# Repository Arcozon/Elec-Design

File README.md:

# Bill of Materials
| Item # | Quantity | Ref | Manufacturer | Manufacturer Part Number |Description | Type
| --: | :--: | :----: | :-----: | :-----: | :-----: | :---: |
| 1 | 1 | R1 | YAGEO | RC0603JR-07330RL | 330 Ω | SMT
| 2 | 2 | R2, R3 | YAGEO | RC0603JR-0710KL | 10 kΩ | SMT
| 3 | 2 | C1, C2 | YAGEO | CC0603JRNPO9BN100 | 10 pF | SMT
| 4 | 3 | C3, C4, C7 | YAGEO | CC0603KRX7R9BB104 | 100 nF | SMT
| 5 | 1 | C6 | YAGEO | CC0603KRX7R9BB104 | 1 uF | SMT
| 6 | 1 | D1 | Hubei KENTO Elec | KT-0603G | Green LED | SMT
| 7 | 1 | D2 | Hubei KENTO Elec | KT-0603R | Red LED | SMT
| 8 | 1 | SW1 | Omron Electronics | B3U-1000P | Push Switch | SMT
| 9 | 1 | Y1 | YXC Crystal Oscillators | X322516MOB4SI | 16 MHz Crystal | SMT
| 10 | 1 | U1 | Microchip Technology | ATmega328P-AN | 32 pin, TQFP Microcontroller  | SMT
| 11 | 2 | J1, J2 | hanxia | HX PH254-01-04-Z-L11.5 straight pin header | 12 pin header, = 2.54mm | THT
| 12 | 1 | J3 | hanxia | HX PH254-01-04-Z-L11.5 straight pin header | 6 pin header, P = 2.54mm | THT

# Pinout
Pins are used and connected, unless specified otherwise
###  U1
| Pin # | Name | Description / Connected to
| --: | :--: | :----: |
| 1 | PD3 | J1-Pin7
| 2 | PD4 | J1-Pin6
| 3 | GND | Ground
| 4 | VCC | Supply voltage
| 5 | GND | Ground, Unused
| 6 | VCC | Supply voltage, Unused
| 7 | XTAL1/PB6 | Oscilation input, Y1-Pin1
| 8 | XTAL2/PB7 | Oscilation input, Y1-Pin3
| 9 | PD5 | J1-Pin5
| 10 | PD6 | J1-Pin4
| 11 | PD7 | J1-Pin3
| 12 | PB0 | J1-Pin2
| 13 | PB1 | J1-Pin1
| 14 | PB2 | Unconnected
| 15 | PB3 | MOSI, J2-Pin11
| 16 | PB4 | MISO, J2-Pin10
| 17 | PB5 | SCK, J2-Pin9
| 18 | AVCC | Supply voltage for ADC
| 19 | ADC6 | Analog input 6, Unconnected
| 20 | AREF | Analog reference
| 21 | GND | Ground, Unused
| 22 | ADC7 | Analog input 7, Unconnected
| 23 | PC0 | Analog input 0, J2-Pin8
| 24 | PC1 | Analog input 1, J2-Pin7
| 25 | PC2 | Analog input 2, J2-Pin6
| 26 | PC3 | Analog input 3, J2-Pin5
| 27 | PC4 | Analog input 4, Unconnected
| 28 | PC5 | Analog input 5, Unconnected
| 29 | RESET/PC6 | Reset signal, J1-Pin10, J2-Pin3, J3-Pin1
| 30 | PD0 | RXI, J1-Pin11, J3-Pin3
| 31 | PD1 | TXO, J1-Pin12, J3-Pin2
| 32 | PD2 | J1-Pin8

###  Y1
| Pin # | Description / Connected to
| --: | :----: |
| 1 | Oscilation output, U1-XTAL1
| 2 | Ground
| 3 | Oscilation output, U1-XTAL2
| 4 | Ground

### J1
| Pin # | Connected to
| --: | :----: |
| 1 | Digital input 9, U1-PB0
| 2 | Digital input 8, U1-PB1
| 3 | Digital input 7, U1-PD7
| 4 | Digital input 6, U1-PD6
| 5 | Digital input 5, U1-PD5
| 6 | Digital input 4, U1-PD4
| 7 | Digital input 3, U1-PD3
| 8 | Digital input 2, U1-PD2
| 9 | Ground
| 10 | U1-Reset, J2-Pin3, J3-Pin1
| 11 | U1-RXI, J3-Pin3
| 12 | U1-TXO, J3-Pin2

### J2
| Pin # | Connected to
| --: | :----: |
| 1 | Power Supply
| 2 | Ground
| 3 | U1-Reset, J1-Pin10, J3-Pin1
| 4 | Supply voltage
| 5 | Analog input 0, U1-PC0
| 6 | Analog input 1, U1-PC1
| 7 | Analog input 2, U1-PC2
| 8 | Analog input 3, U1-PC3
| 9 | U1-PB5, R1
| 10 | MISO, U1-MISO
| 11 | MOSI, U1-MOSI
| 12 | AU1-PB2

### J3
| Pin # | Connected to
| --: | :----: |
| 1 | U1-Reset, J1-Pin10, J2-Pin3
| 2 | U1-TXO, J1-Pin12
| 3 | U1-RXI, J1-Pin11
| 4 | Supply voltage
| 5 | Ground
| 6 | Ground

###  D1, D2
The leds are polarized, the pin order maters
| Pin # | Description
| --: | :----: |
| 1 | Power output
| 2 | Power input
- D1 is connected to Ground (1) and Supply volatage (2)
- D2 is connected to Ground (1) and R1 (2)

### R1, R2, R3
The resistors are not polarized, the pin order does not mater
- R1 is connected to (U1-PB5, J2-Pin9) and D1-P2
- R2 is connected to Ground and D2-P1
- R3 is connected to Supply voltage and (SW1, U1-Reset, J1-Pin10, J2-Pin3)

### C1, C2, C3, C4, C6, C7
The capacitors are not polarized, the pin order does not mater
- C1 is connected to (U1-XTAL1,Y1-Pin1) and Ground
- C2 is connected to (U1-XTAL2,Y1-Pin3) and Ground
- C3 is connected to Supply voltage and U1-AREF
- C4 is connected to SW1 and Ground
- C6 is connected to Supply voltage and Ground
- C7 is connected to Supply voltage and Ground

### SW1
The switch is not polarized, the pin order does not mater
Connected to C4 and (R3, U1-Reset, J1-Pin10, J2-Pin3)

# Notes
- My drawing is a footprint in my lib because i didnt known how to do it otherwise, it also has an error because it has no courtyard
- C5 is missing from provided shematic

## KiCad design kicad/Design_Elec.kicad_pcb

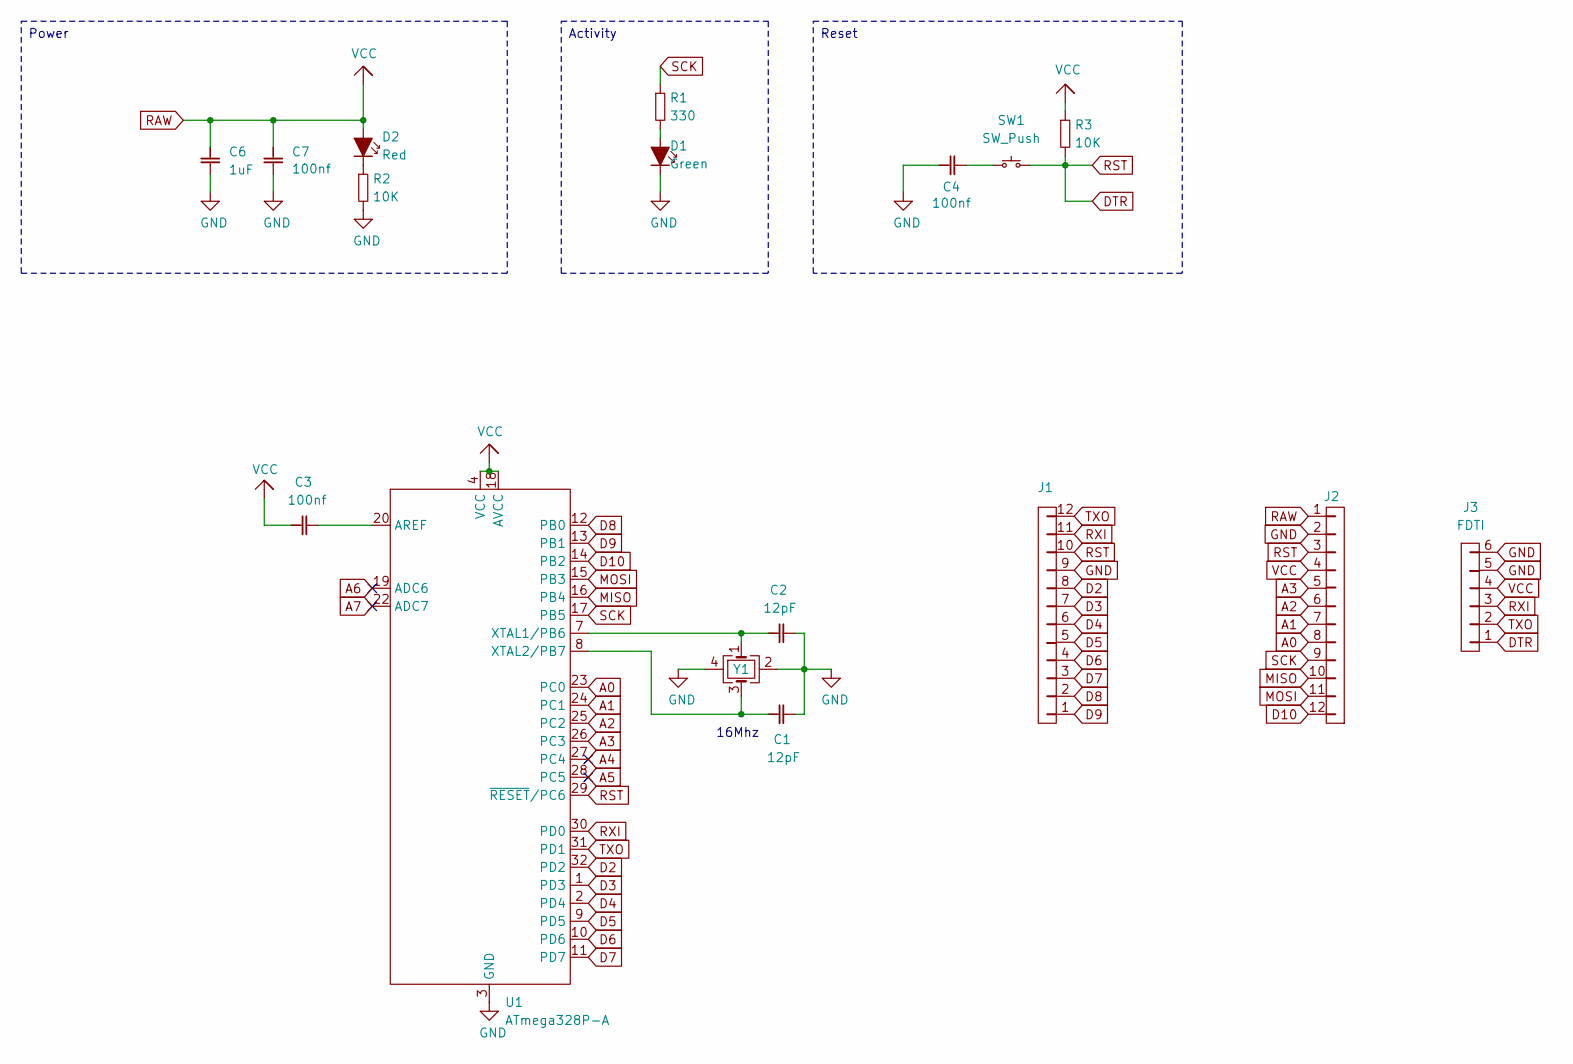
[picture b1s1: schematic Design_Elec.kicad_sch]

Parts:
C1, C2: 12pF; C0603-DA-DimCode_1.7x0.9x0.9mm_P0.4mm
C3, C4, C7: 100nf; C0603-DA-DimCode_1.7x0.9x0.9mm_P0.4mm
C6: 1uF; C0603-DA-DimCode_1.7x0.9x0.9mm_P0.4mm
D1: Green; LED-0603_1.6x0.8x0.6mm_P1.2mm
D2: Red; LED-0603_1.6x0.8x0.6mm_P1.2mm
J1, J2: PinHeader-1x12_30.3x2.5x8.5mm_T3mm_P2.54mm
J3: FDTI; PinHeader-1x06_15.05x2.5x8.5mm_T3mm_P2.54mm
R1: 330; R0603_1.75x0.95x0.55mm_P1.3mm
R2, R3: 10K; R0603_1.75x0.95x0.55mm_P1.3mm
SW1: SW_Push; SW-B3U-1000P_4x2.5x1.7mm_P2.65mm
U1: ATmega328P-A; ATmega328P-AB-TQFP-32_7x7x1.2mm_P0.8mm
Y1: Crystal-YSX321SL_3.2x2.5x0.7mm

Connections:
A0: J2.8, U1.23 (PC0)
A1: J2.7, U1.24 (PC1)
A2: J2.6, U1.25 (PC2)
A3: J2.5, U1.26 (PC3)
A4: U1.27 (PC4)
A5: U1.28 (PC5)
A6: U1.19 (ADC6)
A7: U1.22 (ADC7)
D2: J1.8, U1.32 (PD2)
D3: J1.7, U1.1 (PD3)
D4: J1.6, U1.2 (PD4)
D5: J1.5, U1.9 (PD5)
D6: J1.4, U1.10 (PD6)
D7: J1.3, U1.11 (PD7)
D8: J1.2, U1.12 (PB0)
D9: J1.1, U1.13 (PB1)
D10: J2.12, U1.14 (PB2)
DTR: J1.10, J2.3, J3.1, R3.2, SW1.2, U1.29 (RESET/PC6)
GND: C1.2, C2.2, C4.1, C6.2, C7.2, D1.1, J1.9, J2.2, J3.5, J3.6, R2.2, U1.3 (GND), Y1.2, Y1.4
MISO: J2.10, U1.16 (PB4)
MOSI: J2.11, U1.15 (PB3)
unnamed: C4.2, SW1.1
unnamed: D1.2, R1.2
unnamed: D2.1, R2.1
unnamed: C3.2, U1.20 (AREF)
unnamed: C2.1, U1.7 (XTAL1/PB6), Y1.1
unnamed: C1.1, U1.8 (XTAL2/PB7), Y1.3
RAW: C3.1, C6.1, C7.1, D2.2, J2.1, J2.4, J3.4, R3.1, U1.4 (VCC), U1.18 (AVCC)
RXI: J1.11, J3.3, U1.30 (PD0)
SCK: J2.9, R1.1, U1.17 (PB5)
TXO: J1.12, J3.2, U1.31 (PD1)

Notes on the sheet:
16Mhz
Power
Activity
Reset

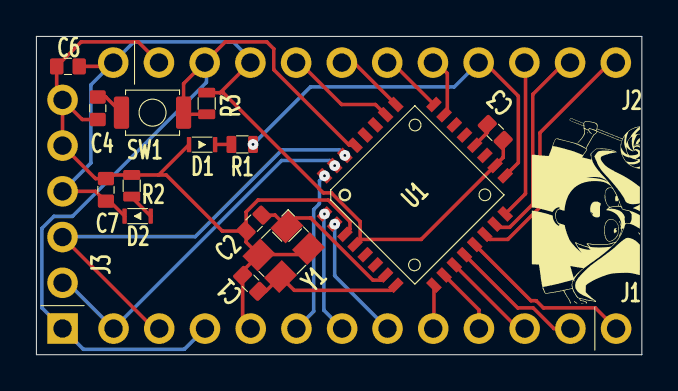
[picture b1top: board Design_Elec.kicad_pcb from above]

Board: 2 copper layers, 33.6 x 17.7 mm, 18 parts (0 on the bottom side), 27 nets.

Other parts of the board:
L: LOGO; LuluMix

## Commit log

2026-05-11 Resistor/capacitor/gnd/vcc/Atmega
2026-05-11 LED Green/Red
2026-05-11 Y:clock generator ?
2026-05-11 Symbols done - J added
2026-05-11 Shematic, Atmega and J1/2
2026-05-11 Shematic - Down is made
2026-05-11 Symbol table is 50mm aligned
2026-05-11 Shematic done ?? idk
2026-05-11 No idea why it doesnt not work no idea why it should
2026-05-12 Pins are numbers, only 2 errors
2026-05-12 DSwitch is done with circles and its pwetty
2026-05-12 No error but i swear its bs
2026-05-12 6 warnings damn
2026-05-12 Errors now
2026-05-12 FootPrint - ATmega32P
2026-05-14 Shematic is better
2026-05-14 R done and atmega fixed
2026-05-14 ADded sw, fixed names for C and R
2026-05-14 PinHeader 12
2026-05-14 Y added
2026-05-14 FootPrint done
2026-05-14 it is linked
2026-05-14 Need to l;ink the thing
2026-05-15 PCB SWAG
2026-05-16 Lulumix
2026-05-18 Cleanup
2026-05-18 Renamed pcb version
2026-05-18 Done ig
2026-05-22 aasdf
2026-05-22 Rename
2026-05-22 README
2026-05-22 Restored shematic
2026-05-22 PDFs
